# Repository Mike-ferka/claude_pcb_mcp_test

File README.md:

You are designing a PCB in KiCad 10 using the KiCad MCP tools. Work in stages and STOP for my approval after each one.

PROJECT
- Name / path: [name], [C:\path]
- Purpose: [one paragraph on what the board does]

REQUIREMENTS
- Input power: [e.g. 12V solar/battery, max current]
- Rails: [e.g. 5V @ 1A, 3.3V @ 500mA]
- MCU / main ICs: [e.g. ESP32-S3-WROOM-1, or "recommend one and justify it"]
- Interfaces/connectors: [sensors, UART, I2C, antenna, headers]
- Board constraints: [size in mm, layer count, mounting holes, enclosure]
- Manufacturing: [e.g. JLCPCB, prefer basic parts, hand-solderable 0805 minimum]

STAGES
1. Architecture: block diagram in text, part choices with JLCPCB/DigiKey part numbers, and a power budget. Wait for approval.
2. Schematic: place parts, wire everything, label nets, run ERC, fix all errors, and report any warnings you're leaving with reasons. Wait.
3. Board setup: outline, layer stack, design rules and netclasses (power traces sized for current). Wait.
4. Placement: propose placement with reasoning (decoupling caps next to pins, regulator thermal areas, antenna keep-out). Wait.
5. Routing: route power and sensitive nets manually; autoroute only the remaining signal nets. Add ground pours and stitching vias. Run DRC. Wait.
6. Outputs: gerbers, drill files, BOM, and position file for [fab].

RULES
- Check every footprint against the datasheet before using it; say which ones you verified.
- Never invent part numbers. If you can't find a part, say so.
- Save the project after each stage.

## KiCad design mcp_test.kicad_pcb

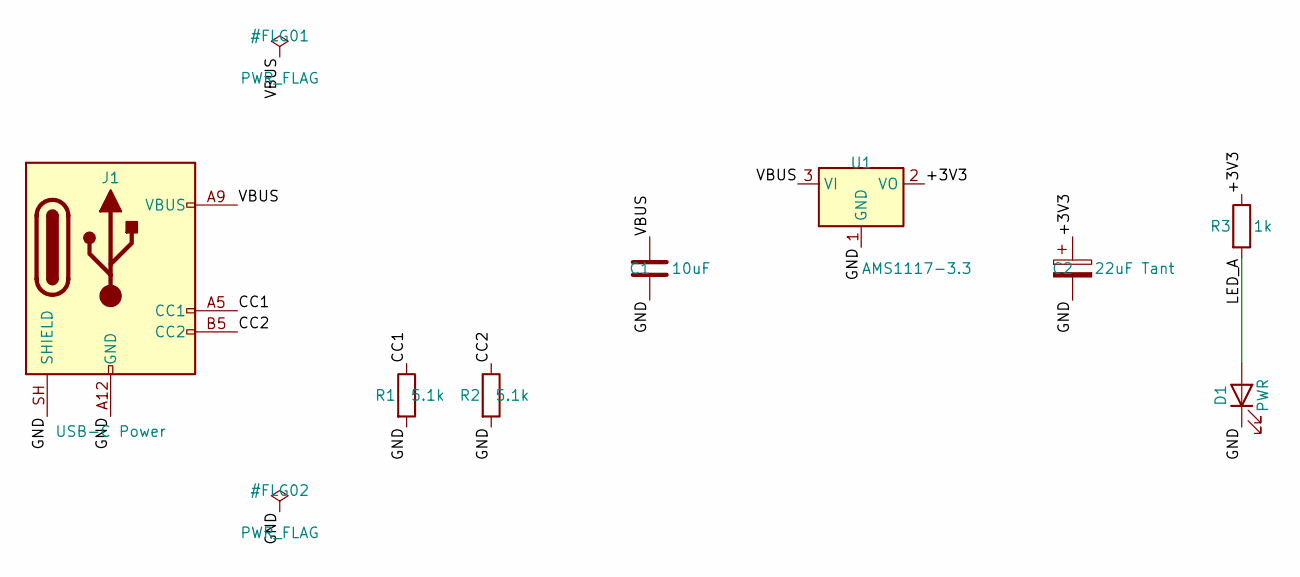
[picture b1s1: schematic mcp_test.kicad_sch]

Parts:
C1: 10uF; C_0805_2012Metric
C2: 22uF Tant; CP_EIA-3528-21_Kemet-B
D1: PWR; LED_0805_2012Metric
J1: USB-C Power; USB_C_Receptacle_GCT_USB4125-xx-x-0190_6P_TopMnt_Horizontal; MPN USB4125-GF-A-0190
R1, R2: 5.1k; R_0805_2012Metric
R3: 1k; R_0805_2012Metric
U1: AMS1117-3.3; SOT-223-3_TabPin2

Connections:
+3V3: C2.1, R3.1, U1.2 (VO)
CC1: J1.A5 (CC1), R1.1
CC2: J1.B5 (CC2), R2.1
GND: C1.2, C2.2, D1.1 (K), J1.A12 (GND), J1.B12 (GND), J1.SH (SHIELD), R1.2, R2.2, U1.1 (GND)
LED_A: D1.2 (A), R3.2
VBUS: C1.1, J1.A9 (VBUS), J1.B9 (VBUS), U1.3 (VI)

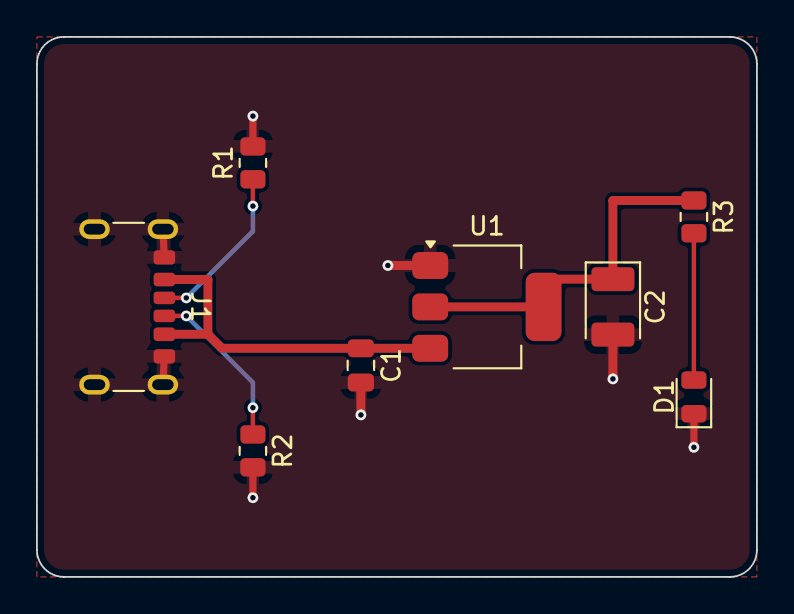
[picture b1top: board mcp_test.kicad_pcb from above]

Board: 2 copper layers, 40.0 x 30.0 mm, 8 parts (0 on the bottom side), 6 nets.
